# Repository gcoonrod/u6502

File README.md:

# u6502 - Single Board Computer
Very basic 6502 SBC based on the [design](http://wilsonminesco.com/6502primer/potpourri.html#BAS_CPU) by Garth Wilson.

## Project Status
A rev 0 board has been fabricated and assembled. Testing is in progress.

### Known Issues
- **LCD Display** - The LCD display correctly shows the two lines that are expected at power up but only displays a single line after a reset. Assumed to be a software issue involving the initialization logic for the LCD controller.
- **ACIA** - No TX traffic is observed from the ACIA. Currently unable to determine the reason. A logic analyzer connected to the chip select and register select signals for the ACIA _seem_ to indicate that the chip is being addressed correctly.

## Design Goals & Project Objectives

- Keep it _almost_ as simple as possible.
    - Start with a proven design to reduce the likelihood of errors.
    - Keep PCB size to less than 100mm^2 to minimize fabrication cost.
    - Use only parts that are currently in production and favor through hole components where possible.
- Support TTL RS232 UART with RTS/CTS flow control.
    - Allow for the loading of programs to memory from serial.
- Support PS2 protocol for keyboard through VIA.
- Support 16 x 2 character LCD display through VIA.
    - (Optional) Support larger character or graphics LCD display.
- (Optional) Support >4 MHz CPU speed.

## Repository Structure

- [boards](./boards/) - Kicad projects containing schematics and layout files for the SBC and any ancillary support devices.
- [docs](./docs/) - Documentation and static assests for the current iteration of the u6502.
- [firmware](./firmware/) - 6502 assembly files and build tooling (cc65) to produce ROMs for the u6502.
- [tools](./tools/) - Software utilities and Arduino sketches used to support the testing and development of the u6502.

## Addres Map

- RAM $0000:3FFF
- ACIA $4400:4403
- VIA2 $5000:500F
- VIA1 $6000:600F
- ROM $8000:FFFF

## Parts Selection

- CPU - W65C02S (PLCC) WDC current production 65C02
- Memory - AS7C256B-15PIN (DIP) SRAM chosen for package size more than speed
- ROM - Any 28C256 JEDEC compatible EEPROM (DIP) 
- Address Decoding - 74HC00 (DIP)
- IRQ Control - 74HC21 (DIP)
- GPIO - 2 W65C22S VIAs (PLCC)
- Serial IO - W65C51N ACIA (DIP)
- Power Regulation - LM7805 (TO220) compatible linear regulator
- Oscillators - 1MHz CPU clock & 1.8432 MHz for baud clock generation
- Reset control - DS1813 (TO92)

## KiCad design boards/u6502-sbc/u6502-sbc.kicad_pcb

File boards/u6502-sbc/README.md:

# u6502 - SBC PCB Design Project
Kicad project for u6502.

[Schematic](../../docs/schematic.pdf)

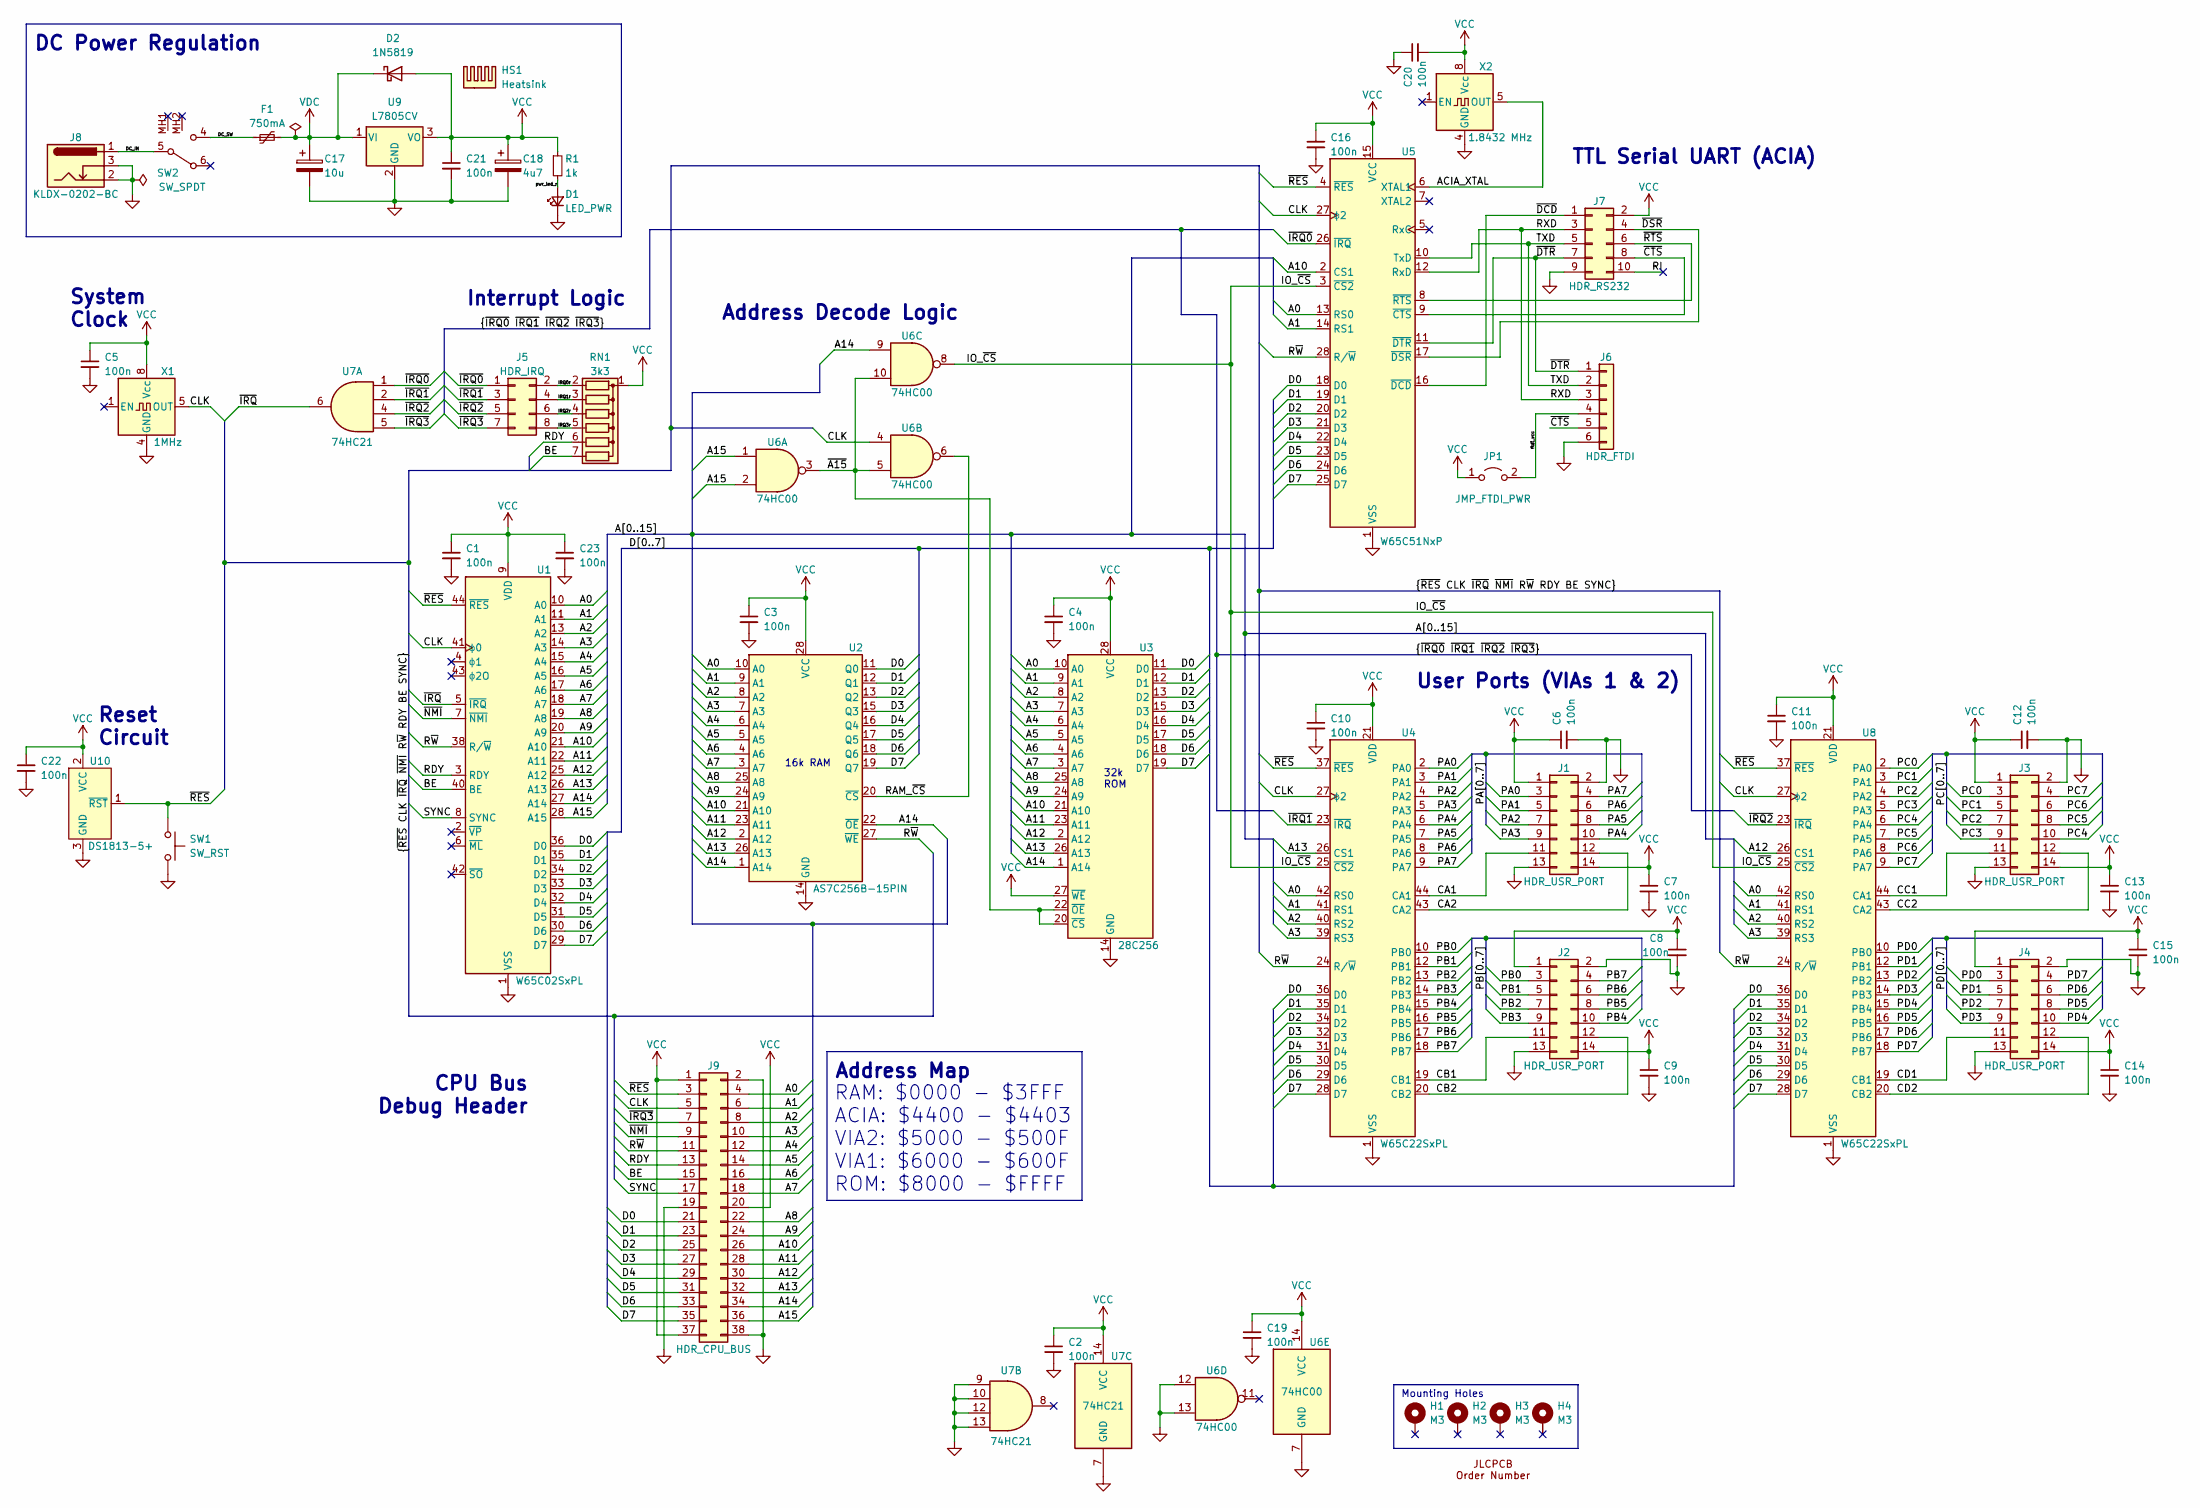
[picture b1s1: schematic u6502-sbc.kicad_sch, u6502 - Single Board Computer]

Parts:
C1, C2, C3, C4, C5, C6, C7, C8, C9, C10, C11, C12, C13, C14, C15, C16, C19, C20, C21, C22, C23: 100n; C_Rect_L4.0mm_W2.5mm_P2.50mm; Mfr Part K104K15X7RF5TL2; Mouser Part 594-K104K15X7RF5TL2
C17: 10u; CP_Radial_D8.0mm_P3.50mm; Mfr Part ESL106M200AG9AA; Mouser Part 80-ESL106M200AG9AA
C18: 4u7; CP_Radial_D5.0mm_P2.00mm; Mfr Part EEU-FR1H4R7B; Mouser Part 667-EEU-FR1H4R7B
D1: LED_PWR; LED_D3.0mm; Mfr Part WP132XID; Mouser Part 604-WP132XID
D2: 1N5819; D_DO-41_SOD81_P7.62mm_Horizontal; Mfr Part 1N5819-T; Mouser Part 621-1N5819
F1: 750mA; Fuse_BelFuse_0ZRE0075FF_L11.5mm_W4.8mm; Mfr Part 0ZRG0075FF1E; Mouser Part 530-0ZRG0075FF1E
H1, H2, H3, H4: M3; MountingHole_3.2mm_M3_Pad
HS1: Heatsink
J1, J2, J3, J4: HDR_USR_PORT; PinHeader_2x07_P2.54mm_Vertical
J5: HDR_IRQ; PinHeader_2x04_P2.54mm_Vertical
J6: HDR_FTDI; PinSocket_1x06_P2.54mm_Vertical
J7: HDR_RS232; PinHeader_2x05_P2.54mm_Vertical
J8: KLDX-0202-BC; BarrelJack_Kycon_KLDX-0202-xC_Horizontal; Mfr Part KLDX-0202-BC; Mouser Part 806-KLDX-0202-BC
J9: HDR_CPU_BUS; PinHeader_2x19_P2.54mm_Vertical
JP1: JMP_FTDI_PWR; PinHeader_1x02_P2.54mm_Vertical
R1: 1k; R_Axial_DIN0204_L3.6mm_D1.6mm_P5.08mm_Horizontal
RN1: 3k3; R_Array_SIP7
SW1: SW_RST; SW_PUSH_6mm
SW2: SW_SPDT; GW12RCV; Mfr Part GW12RCV; Mouser Part 633-GW12RCV
SYM1: OrderNumber
U1: W65C02SxPL; PLCC-44_THT-Socket
U2: AS7C256B-15PIN; DIP-28_W7.62mm_Socket
U3: 28C256; Aries 28-526-10; Mfr Part 28-526-10; Mouser Part 535-28-526-10
U4, U8: W65C22SxPL; PLCC-44_THT-Socket
U5: W65C51NxP; DIP-28_W15.24mm
U6: 74HC00; DIP-14_W7.62mm_Socket; Mfr Part SN74HC00AN; Mouser Part 595-SN74HC00AN
U7: 74HC21; DIP-14_W7.62mm_Socket; Mfr Part SN74HC21N; Mouser Part 595-SN74HC21N
U9: L7805CV; TO-220-3_Horizontal_TabDown; Mfr Part L7805CV; Mouser Part 511-L7805CV
U10: DS1813-5+; TO-92_Inline_Wide; Mfr Part DS1813-5+; Mouser Part 700-DS1813-5T&R
X1: 1MHz; Oscillator_DIP-8
X2: 1.8432 MHz; Oscillator_DIP-8; Mfr Part MXO45HS-3C-1M8432; Mouser Part 774-MXO45HS-3C-1.8

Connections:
/A0: J9.4, U1.10 (A0), U2.10 (A0), U3.10 (A0), U4.42 (RS0), U5.13 (RS0), U8.42 (RS0); also elsewhere on the board
/A1: J9.6, U1.11 (A1), U2.9 (A1), U3.9 (A1), U4.41 (RS1), U5.14 (RS1), U8.41 (RS1); also elsewhere on the board
/A2: J9.8, U1.13 (A2), U2.8 (A2), U3.8 (A2), U4.40 (RS2), U8.40 (RS2); also elsewhere on the board
/A3: J9.10, U1.14 (A3), U2.7 (A3), U3.7 (A3), U4.39 (RS3), U8.39 (RS3); also elsewhere on the board
/A4: J9.12, U1.15 (A4), U2.6 (A4), U3.6 (A4); also elsewhere on the board
/A5: J9.14, U1.16 (A5), U2.5 (A5), U3.5 (A5); also elsewhere on the board
/A6: J9.16, U1.17 (A6), U2.4 (A6), U3.4 (A6); also elsewhere on the board
/A7: J9.18, U1.18 (A7), U2.3 (A7), U3.3 (A7); also elsewhere on the board
/A8: J9.22, U1.19 (A8), U2.25 (A8), U3.25 (A8); also elsewhere on the board
/A9: J9.24, U1.20 (A9), U2.24 (A9), U3.24 (A9); also elsewhere on the board
/A10: J9.26, U1.21 (A10), U2.21 (A10), U3.21 (A10), U5.2 (CS1); also elsewhere on the board
/A11: J9.28, U1.22 (A11), U2.23 (A11), U3.23 (A11); also elsewhere on the board
/A12: J9.30, U1.25 (A12), U2.2 (A12), U3.2 (A12), U8.26 (CS1); also elsewhere on the board
/A13: J9.32, U1.26 (A13), U2.26 (A13), U3.26 (A13), U4.26 (CS1); also elsewhere on the board
/A14: J9.34, U1.27 (A14), U2.1 (A14), U2.22 (~OE), U3.1 (A14), U6.9; also elsewhere on the board
/A15: J9.36, U1.28 (A15), U6.1, U6.2; also elsewhere on the board
/ACIA_XTAL: U5.6 (XTAL1), X2.5 (OUT)
/BE: J9.15, RN1.7 (R6), U1.40 (BE); also elsewhere on the board
/CA1: J1.11, U4.44 (CA1)
/CA2: J1.12, U4.43 (CA2)
/CB1: J2.11, U4.19 (CB1)
/CB2: J2.12, U4.20 (CB2)
/CC1: J3.11, U8.44 (CA1)
/CC2: J3.12, U8.43 (CA2)
/CD1: J4.11, U8.19 (CB1)
/CD2: J4.12, U8.20 (CB2)
/CLK: J9.5, U1.41 (ϕ0), U4.27 (ϕ2), U5.27 (ϕ2), U6.4, U8.27 (ϕ2), X1.5 (OUT); also elsewhere on the board
/D0: J9.21, U1.36 (D0), U2.11 (Q0), U3.11 (D0), U4.36 (D0), U5.18 (D0), U8.36 (D0); also elsewhere on the board
/D1: J9.23, U1.35 (D1), U2.12 (Q1), U3.12 (D1), U4.35 (D1), U5.19 (D1), U8.35 (D1); also elsewhere on the board
/D2: J9.25, U1.34 (D2), U2.13 (Q2), U3.13 (D2), U4.34 (D2), U5.20 (D2), U8.34 (D2); also elsewhere on the board
/D3: J9.27, U1.33 (D3), U2.15 (Q3), U3.15 (D3), U4.32 (D3), U5.21 (D3), U8.32 (D3); also elsewhere on the board
/D4: J9.29, U1.32 (D4), U2.16 (Q4), U3.16 (D4), U4.31 (D4), U5.22 (D4), U8.31 (D4); also elsewhere on the board
/D5: J9.31, U1.31 (D5), U2.17 (Q5), U3.17 (D5), U4.30 (D5), U5.23 (D5), U8.30 (D5); also elsewhere on the board
/D6: J9.33, U1.30 (D6), U2.18 (Q6), U3.18 (D6), U4.29 (D6), U5.24 (D6), U8.29 (D6); also elsewhere on the board
/D7: J9.35, U1.29 (D7), U2.19 (Q7), U3.19 (D7), U4.28 (D7), U5.25 (D7), U8.28 (D7); also elsewhere on the board
/DC_IN: J8.1, SW2.5 (COM)
/DC_SW: F1.1, SW2.4 (NO)
/IO_~CS: U4.25 (~CS2), U5.3 (~CS2), U6.8, U8.25 (~CS2)
/IRQ0r: J5.2, RN1.2 (R1)
/IRQ1r: J5.4, RN1.3 (R2)
/IRQ2r: J5.6, RN1.4 (R3)
/IRQ3r: J5.8, RN1.5 (R4)
/PA0: J1.3, U4.2 (PA0)
/PA1: J1.5, U4.3 (PA1)
/PA2: J1.7, U4.4 (PA2)
/PA3: J1.9, U4.5 (PA3)
/PA4: J1.10, U4.6 (PA4)
/PA5: J1.8, U4.7 (PA5)
/PA6: J1.6, U4.8 (PA6)
/PA7: J1.4, U4.9 (PA7)
/PB0: J2.3, U4.10 (PB0)
/PB1: J2.5, U4.12 (PB1)
/PB2: J2.7, U4.13 (PB2)
/PB3: J2.9, U4.14 (PB3)
/PB4: J2.10, U4.15 (PB4)
/PB5: J2.8, U4.16 (PB5)
/PB6: J2.6, U4.17 (PB6)
/PB7: J2.4, U4.18 (PB7)
/PC0: J3.3, U8.2 (PA0)
/PC1: J3.5, U8.3 (PA1)
/PC2: J3.7, U8.4 (PA2)
/PC3: J3.9, U8.5 (PA3)
/PC4: J3.10, U8.6 (PA4)
/PC5: J3.8, U8.7 (PA5)
/PC6: J3.6, U8.8 (PA6)
/PC7: J3.4, U8.9 (PA7)
/PD0: J4.3, U8.10 (PB0)
/PD1: J4.5, U8.12 (PB1)
/PD2: J4.7, U8.13 (PB2)
/PD3: J4.9, U8.14 (PB3)
/PD4: J4.10, U8.15 (PB4)
/PD5: J4.8, U8.16 (PB5)
/PD6: J4.6, U8.17 (PB6)
/PD7: J4.4, U8.18 (PB7)
/RAM_~CS: U2.20 (~CS), U6.6
/RDY: J9.13, RN1.6 (R5), U1.3 (RDY); also elsewhere on the board
/RI: J7.10
/RXD: J6.3, J7.3, U5.12 (RxD)
/R~W: J9.11, U1.38 (R/~W), U2.27 (~WE), U4.24 (R/~W), U5.28 (R/~W), U8.24 (R/~W); also elsewhere on the board
/SYNC: J9.17, U1.8 (SYNC); also elsewhere on the board
/TXD: J6.2, J7.5, U5.10 (TxD)
/ftdi_vcc: J6.4, JP1.2 (B)
/pwr_led_r: D1.2 (A), R1.2
/~A15: U3.20 (~CS), U3.22 (~OE), U6.3, U6.5, U6.10
/~CTS: J6.5, J7.8, U5.9 (~CTS)
/~DCD: J7.1, U5.16 (~DCD)
/~DSR: J7.4, U5.17 (~DSR)
/~DTR: J6.1, J7.7, U5.11 (~DTR)
/~IRQ0: J5.1, U5.26 (~IRQ), U7.1
/~IRQ1: J5.3, U4.23 (~IRQ), U7.2
/~IRQ2: J5.5, U7.4, U8.23 (~IRQ)
/~IRQ3: J5.7, J9.7, U7.5; also elsewhere on the board
/~IRQ: U1.5 (~IRQ), U7.6
/~NMI: J9.9, U1.7 (~NMI); also elsewhere on the board
/~RES: J9.3, SW1.1, U1.44 (~RES), U4.37 (~RES), U5.4 (~RES), U8.37 (~RES), U10.1 (~RST); also elsewhere on the board
/~RTS: J7.6, U5.8 (~RTS)
GND: C1.2, C2.2, C3.2, C4.2, C5.2, C6.2, C7.2, C8.2, C9.2, C10.2, C11.2, C12.2, C13.2, C14.2, C15.2, C16.2, C17.2, C18.2, C19.2, C20.1, C21.2, C22.2, C23.2, D1.1 (K), J1.2, J1.13, J2.2, J2.13, J3.2, J3.13, J4.2, J4.13, J6.6, J7.9, J8.2, J8.3, J9.2, J9.19, J9.38, SW1.2, U1.1 (VSS), U1.23 (VSS), U1.24 (VSS), U2.14 (GND), U3.14 (GND), U4.1 (VSS), U5.1 (VSS), U6.7 (GND), U6.12, U6.13, U7.7 (GND), U7.9, U7.10, U7.12, U7.13, U8.1 (VSS), U9.2 (GND), U10.3 (GND), X1.4 (GND), X2.4 (GND); also elsewhere on the board
VCC: C1.1, C2.1, C3.1, C4.1, C5.1, C6.1, C7.1, C8.1, C9.1, C10.1, C11.1, C12.1, C13.1, C14.1, C15.1, C16.1, C18.1, C19.1, C20.2, C21.1, C22.1, C23.1, D2.2 (A), J1.1, J1.14, J2.1, J2.14, J3.1, J3.14, J4.1, J4.14, J7.2, J9.1, J9.20, J9.37, JP1.1 (A), R1.1, RN1.1 (common), U1.9 (VDD), U1.37 (VDD), U2.28 (VCC), U3.27 (~WE), U3.28 (VCC), U4.21 (VDD), U5.15 (VCC), U6.14 (VCC), U7.14 (VCC), U8.21 (VDD), U9.3 (VO), U10.2 (VCC), X1.8 (Vcc), X2.8 (Vcc); also elsewhere on the board
VDC: C17.1, D2.1 (K), F1.2, U9.1 (VI)

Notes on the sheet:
User Ports (VIAs 1 & 2)
TTL Serial UART (ACIA)
Interrupt Logic
Mounting Holes
RAM: $0000 - $3FFF ACIA: $4400 - $4403 VIA2: $5000 - $500F VIA1: $6000 - $600F ROM: $8000 - $FFFF
Address Decode Logic
CPU Bus Debug Header
Reset Circuit
32k ROM
DC Power Regulation
16k RAM
Address Map
System Clock

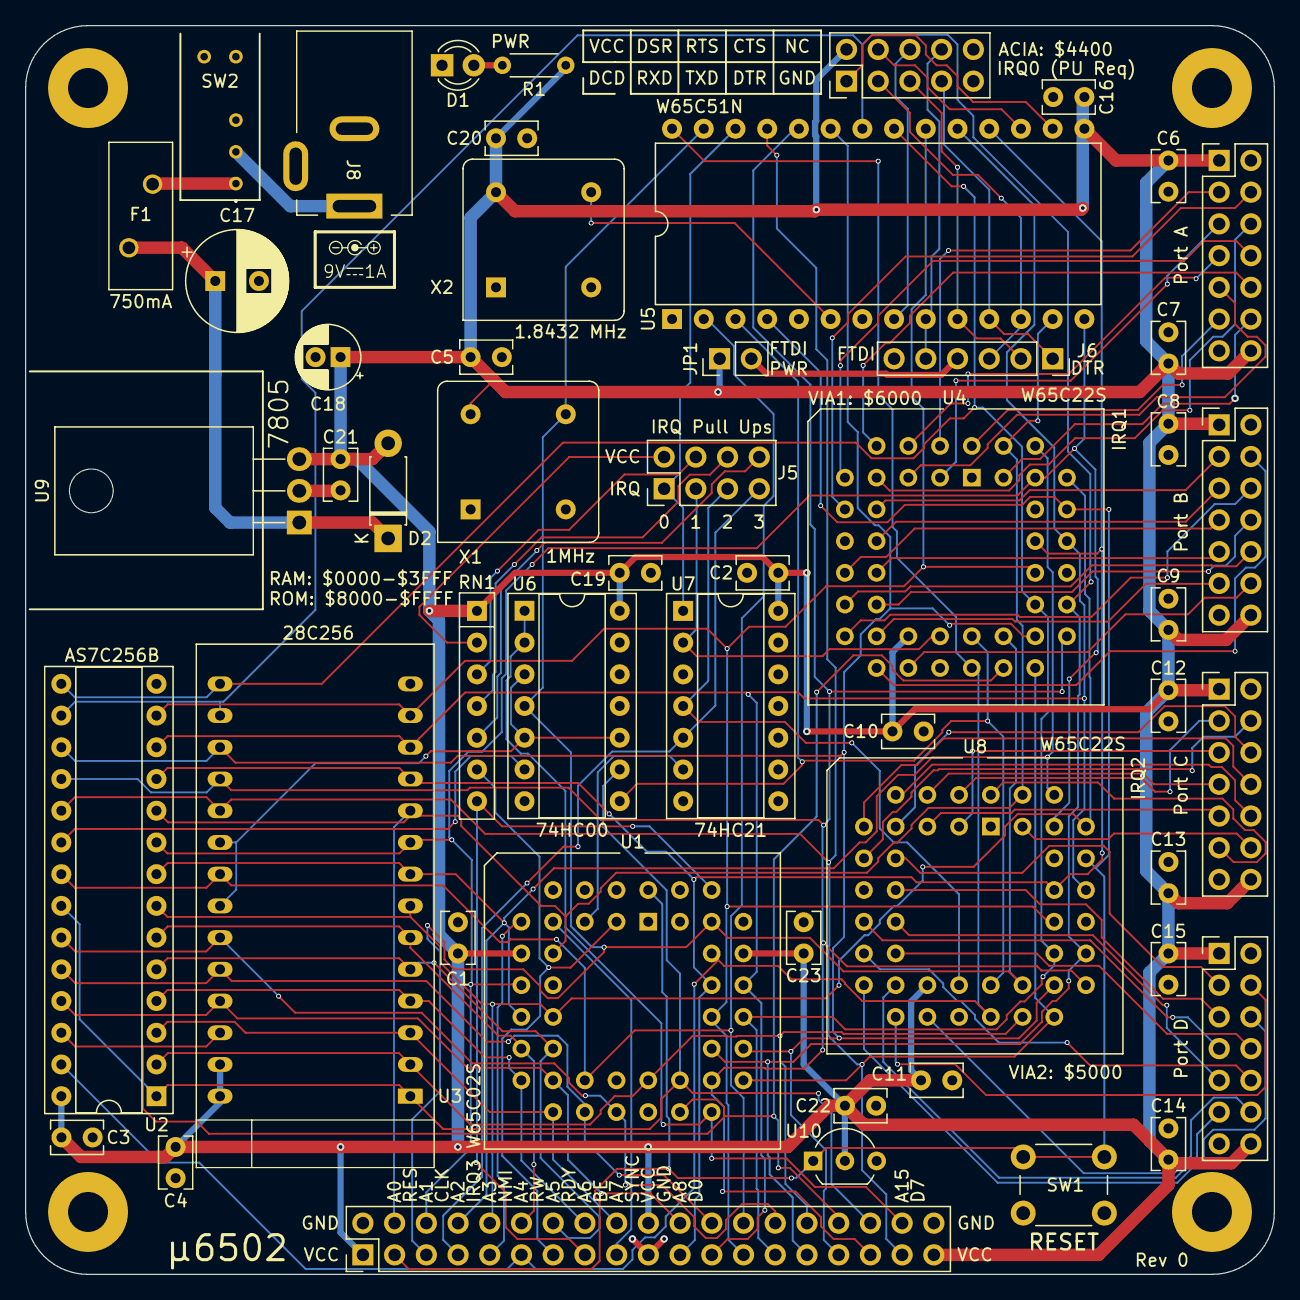
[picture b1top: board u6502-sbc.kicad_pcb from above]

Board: 4 copper layers, 100.0 x 100.0 mm, 57 parts (1 on the bottom side), 98 nets.

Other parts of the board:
locked: HDR_CPU_BUS; PinHeader_2x19_P2.54mm_Vertical

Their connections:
/A0: locked.4; also elsewhere on the board
/A1: locked.6; also elsewhere on the board
/A2: locked.8; also elsewhere on the board
/A3: locked.10; also elsewhere on the board
/A4: locked.12; also elsewhere on the board
/A5: locked.14; also elsewhere on the board
/A6: locked.16; also elsewhere on the board
/A7: locked.18; also elsewhere on the board
/A8: locked.22; also elsewhere on the board
/A9: locked.24; also elsewhere on the board
/A10: locked.26; also elsewhere on the board
/A11: locked.28; also elsewhere on the board
/A12: locked.30; also elsewhere on the board
/A13: locked.32; also elsewhere on the board
/A14: locked.34; also elsewhere on the board
/A15: locked.36; also elsewhere on the board
/BE: locked.15; also elsewhere on the board
/CLK: locked.5; also elsewhere on the board
/D0: locked.21; also elsewhere on the board
/D1: locked.23; also elsewhere on the board
/D2: locked.25; also elsewhere on the board
/D3: locked.27; also elsewhere on the board
/D4: locked.29; also elsewhere on the board
/D5: locked.31; also elsewhere on the board
/D6: locked.33; also elsewhere on the board
/D7: locked.35; also elsewhere on the board
/RDY: locked.13; also elsewhere on the board
/R~W: locked.11; also elsewhere on the board
/SYNC: locked.17; also elsewhere on the board
/~IRQ3: locked.7; also elsewhere on the board
/~NMI: locked.9; also elsewhere on the board
/~RES: locked.3; also elsewhere on the board
GND: locked.2, locked.19, locked.38; also elsewhere on the board
VCC: locked.1, locked.20, locked.37; also elsewhere on the board

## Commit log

2023-08-25 Initial layout and routing wip
2023-08-28 Board rev 0 ordered
2023-09-09 Add basic build tooling.
2023-09-09 Minor updates from rev 0.
2023-09-10 Add pio project for debugmonitor.
2023-09-10 hello-world works.
2023-10-09 Update docs for rev 0.
2023-10-17 docs update
